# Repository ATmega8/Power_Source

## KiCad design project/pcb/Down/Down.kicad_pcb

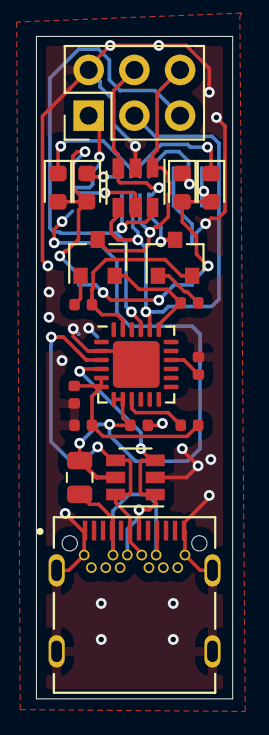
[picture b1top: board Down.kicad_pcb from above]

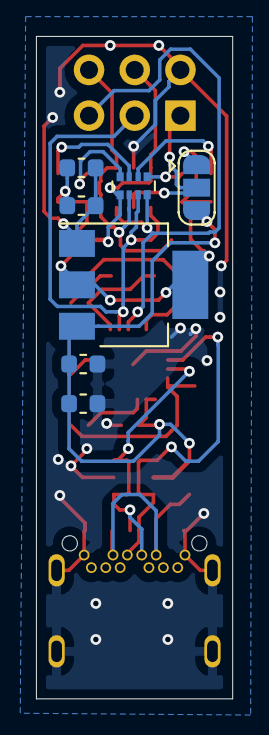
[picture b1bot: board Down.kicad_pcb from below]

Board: 2 copper layers, 10.9 x 36.8 mm, 26 parts (7 on the bottom side), 22 nets.

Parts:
C1, C3: 10uF; C_0603_1608Metric
C2, C4: 1uF; C_0603_1608Metric
C5: 4.7uF; C_0402_1005Metric
C6, C8: 1uF; C_0402_1005Metric
C7: 0.1uF; C_0402_1005Metric
D1, D2, D3, D4: LED; LED_0603_1608Metric
F1: PPTC; Fuse_0805_2012Metric
J1: Conn_02x03_Odd_Even; PinHeader_2x03_P2.54mm_Vertical
JP1: SolderJumper_3_Open; SolderJumper-3_P1.3mm_Open_RoundedPad1.0x1.5mm
Q1, Q2: S8050; SOT-23
R1: 4.7K; R_0402_1005Metric
R2, R3: 1K; R_0402_1005Metric
RN1: 1K; R_Array_Convex_4x0402
U1: UJ31-CH-3-SMT-TR; UJ31-Ch-3-SMT-TR
U2, U3: SRV05-4; SOT-23-6
U4: AMS1117-LDO; SOT-223
U5: CP2104; QFN-24-1EP_4x4mm_P0.5mm_EP2.6x2.6mm

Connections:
+3V3: C3.1, C4.1, D1.2, D2.2, D3.2, D4.2, JP1.1, U4.2, U4.4
/CP2104/DTR: Q2.2, R2.1, U5.23
/CP2104/RTS: Q1.2, R3.1, U5.19
/CP2104/VDD3V45: C7.2, C8.2, R1.2, U5.5, U5.6
/D+: U1.A6, U1.B6, U2.4, U2.6, U5.3
/D-: U1.A7, U1.B7, U2.1, U2.3, U5.4
/EN: J1.6, Q1.3, RN1.2, U3.1
/IO0: J1.4, Q2.3, RN1.1, U3.3
/RXD: J1.3, RN1.3, U3.4, U5.20
/TXD: J1.5, RN1.4, U3.6, U5.21
GND: C1.2, C2.2, C3.2, C4.2, C5.2, C6.1, C7.1, C8.1, J1.2, U1.A1, U1.A12, U1.B1, U1.B12, U1.SH1, U1.SH2, U1.SH3, U1.SH4, U2.2, U3.2, U4.1, U5.2, U5.25
unnamed: C5.1, U5.16
unnamed: D1.1, RN1.8
unnamed: D2.1, RN1.7
unnamed: D3.1, RN1.6
unnamed: D4.1, RN1.5
unnamed: F1.2, U1.A4, U1.A9, U1.B4, U1.B9
unnamed: Q1.1, R2.2
unnamed: Q2.1, R3.2
unnamed: R1.1, U5.9
VBUS: C1.1, C2.1, C6.2, F1.1, JP1.3, U2.5, U4.3, U5.7, U5.8
VS: J1.1, JP1.2, U3.5

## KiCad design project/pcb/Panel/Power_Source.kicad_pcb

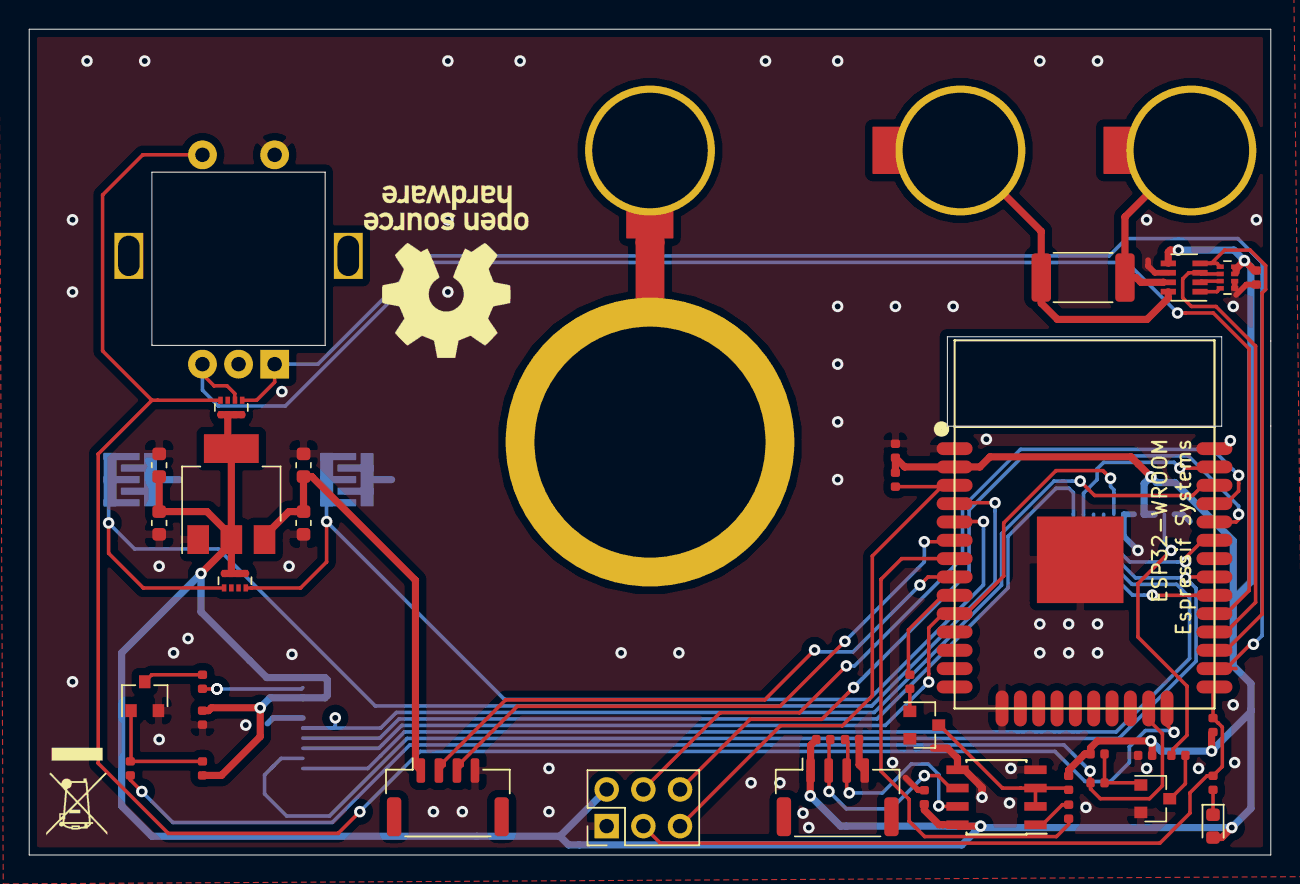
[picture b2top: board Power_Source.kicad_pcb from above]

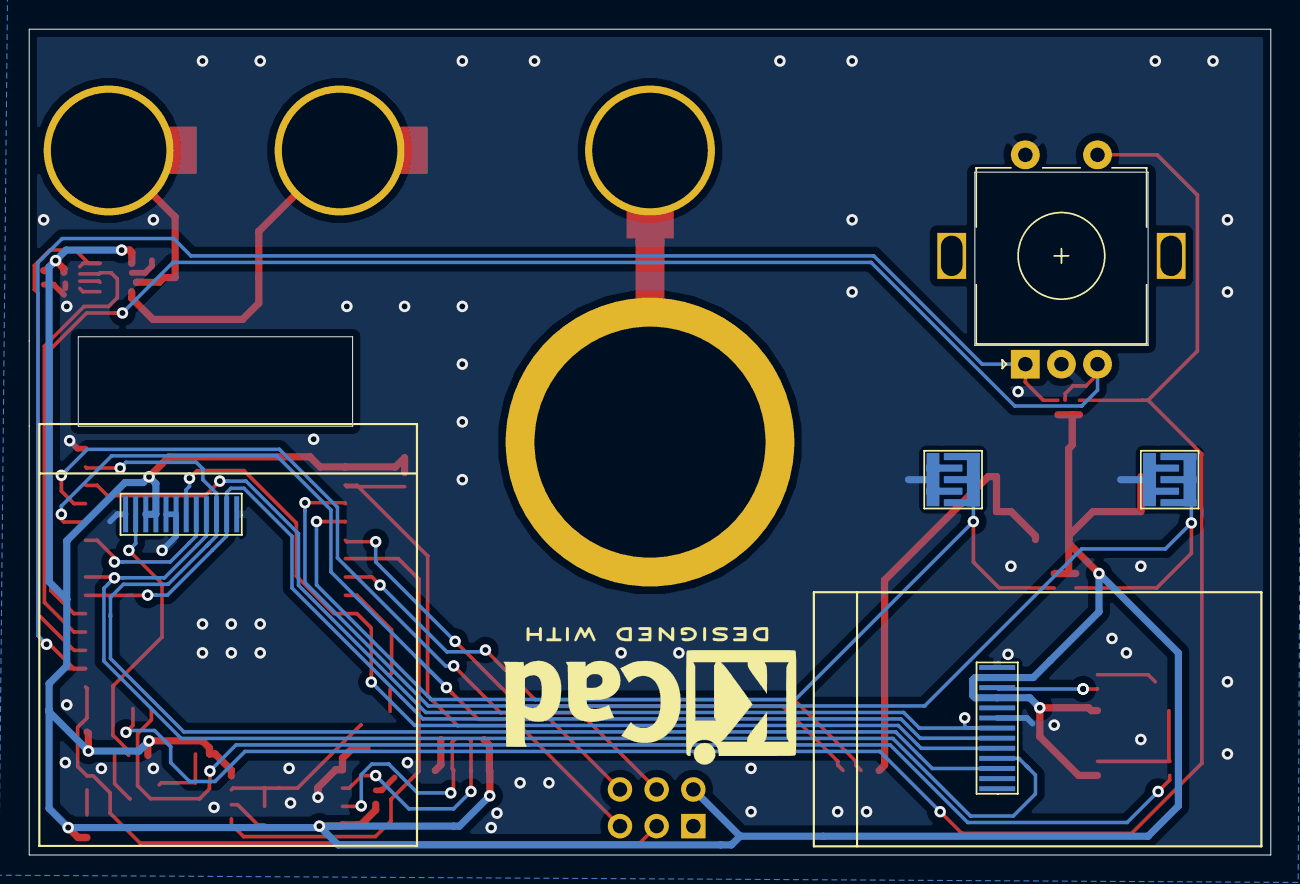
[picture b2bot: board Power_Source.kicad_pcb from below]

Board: 2 copper layers, 86.0 x 57.2 mm, 47 parts (5 on the bottom side), 42 nets.

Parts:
C1, C2, C3, C8, C9: 0.1uF; C_0402_1005Metric
C4, C6: 10uF; C_0603_1608Metric
C5, C7: 1uF; C_0603_1608Metric
D1: LED; LED_0603_1608Metric
J1: Debug; PinHeader_2x03_P2.54mm_Vertical
J2: VIN+; JS-910B-4MM
J3: VIN-; JS-910B-4MM
J4: CON1; Molex_CLIK-Mate_502386-0470_1x04-1MP_P1.25mm_Horizontal
J5: CON2; Molex_CLIK-Mate_502386-0470_1x04-1MP_P1.25mm_Horizontal
J6: GND; JS-910B-4MM
J7: GND; PWR_BTN
LCD1: IPS1.3'240x240
LCD2: IPS1.14'240x135
Q1, Q2, Q4: S8050; SOT-23
R1, R2, R5, R8: 10K; R_0402_1005Metric
R3, R4, R7, R13: 1K; R_0402_1005Metric
R6, R9: 10; R_0402_1005Metric
R10: 0.1; R_2512_6332Metric
R11, R12, R14, R15: 4.7K; R_0402_1005Metric
RN1, RN2, RN3: 10K; R_Array_Concave_4x0402
SW1: Rotary_Encoder_Switch; RotaryEncoder_Alps_EC11E-Switch_Vertical_H20mm
SW2, SW3: SW_Push; PCB_BTN
U1: ESP32-WROOM
U2: AMS1117-LDO; SOT-223
U3: INA219; SOT-23-8
U4: SP3485EN; SOIC-8_3.9x4.9mm_P1.27mm

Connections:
+3V3: C1.1, C2.2, C3.2, C6.1, C7.1, C8.2, C9.2, D1.2, J1.2, J5.1, LCD1.3, LCD1.4, LCD2.10, LCD2.12, R1.2, R2.1, R5.1, R8.1, R12.1, R14.1, RN1.3, RN1.4, RN2.5, RN2.6, RN2.7, RN2.8, RN3.5, RN3.6, RN3.7, RN3.8, U1.2, U2.2, U2.4, U3.5, U4.8
/BTN0: RN3.1, SW2.1, U1.4
/BTN1: RN3.4, SW3.1, U1.5
/ENC_A: RN2.1, SW1.A, U1.26
/ENC_B: RN2.2, SW1.B, U1.29
/ENC_D: RN2.4, SW1.S1, U1.24
/ESP32/EN: J1.5, R1.1, U1.3
/ESP32/GPIO0: J1.3, R2.2, R3.1, U1.25
/ESP32/RXD: J1.6, U1.34
/ESP32/TXD: J1.4, U1.35
/INA219/VIN+: J2.1, R10.1, U3.8
/INA219/VIN-: J3.1, R10.2, U3.7
/LCD240x135/LEDK: LCD2.11, R9.1
/LCD240x240/LEDK: LCD1.2, R6.1
/LCD_BLK: R4.2, R7.2, U1.23
/LCD_CLK: LCD1.9, LCD2.4, U1.31
/LCD_CS0: LCD1.8, U1.33
/LCD_CS1: LCD2.7, U1.36
/LCD_DC: LCD1.7, LCD2.5, U1.10
/LCD_MOSI: LCD1.10, LCD2.3, U1.37
/LCD_RES: LCD1.11, LCD2.6, U1.30
/SCL: RN1.5, U1.27, U3.4
/SDA: RN1.6, U1.28, U3.3
/SP3485/A: J5.2, R14.2, U4.6
/SP3485/B: J5.3, R15.1, U4.7
/UART1_RXD: J4.3, U1.6
/UART1_TXD: J4.2, U1.8
/UART2_RXD: R13.2, U1.7
/UART2_TXD: R11.2, U1.9
Earth: J6.1, J7.1
GND: C1.2, C2.1, C3.1, C4.2, C5.2, C6.2, C7.2, C8.1, C9.1, J1.1, J4.4, J5.4, LCD1.1, LCD1.5, LCD1.6, LCD1.12, LCD2.8, LCD2.13, Q1.2, Q2.2, Q4.2, R15.2, RN1.1, RN1.2, SW1.C, SW1.S2, SW2.2, SW3.2, U1.1, U1.15, U1.38, U1.39, U2.1, U3.6, U4.4, U4.5
unnamed: D1.1, R3.2
unnamed: Q1.1, R4.1, R5.2
unnamed: Q1.3, R6.2
unnamed: Q2.1, R7.1, R8.2
unnamed: Q2.3, R9.2
unnamed: Q4.1, R11.1
unnamed: Q4.3, R12.2, U4.2, U4.3
unnamed: R13.1, U4.1
unnamed: RN1.7, U3.2
unnamed: RN1.8, U3.1
VCC: C4.1, C5.1, J4.1, U2.3

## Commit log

2019-07-15 Revert "Initial commit"
    This reverts commit 239e0073c571b5f78ca06b02d50d2225723b6681.
2019-07-15 feature(kicad): lcd and esp32 lib
2019-07-17 feature(pcb): add 3d
2019-07-17 esp32 module ok
2019-07-17 feature(pcb): power ok
2019-07-20 feature(components): add components
2019-07-21 add code
2019-07-21 feature(lib): add kicad lib
2019-07-21 feature(pcb): start layout
2019-07-22 feature(pcb): sch ok
2019-07-23 feature(pcb): add hidden_footprint.py
2019-07-23 feature(pcb): update pcb
2019-07-23 feature(pcb): route ok
2019-07-23 feature(pcb): pcb ok
2019-07-23 feature(pcb): gerber ok
2019-07-24 feature(pcb): output ok
2019-07-24 feature(pcb): add USB3.1 lib
2019-07-24 feature(pcb): update USB3.1
2019-07-24 feature(pcb): update path
2019-07-25 feature(pcb): add download
2019-07-26 feature(pcb): add pcb down
2019-07-26 feature(pcb): hidden Down footprint
2019-07-26 feature(pcb): pcb down ok
2019-07-28 feature(code): code ok
2019-07-28 bugfix(3d): change 3d size
2019-08-03 add STM32
